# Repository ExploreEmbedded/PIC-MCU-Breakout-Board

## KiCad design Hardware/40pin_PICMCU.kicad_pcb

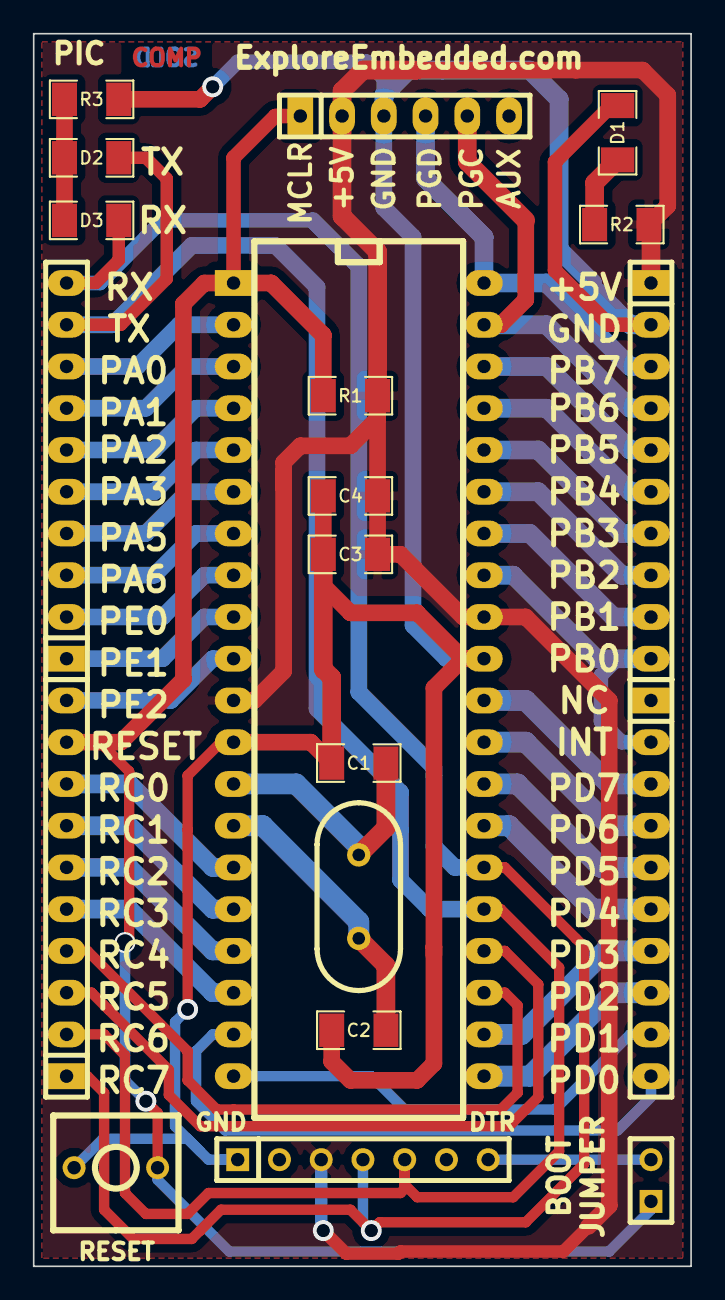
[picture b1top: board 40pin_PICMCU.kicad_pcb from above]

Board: 2 copper layers, 40.0 x 75.0 mm, 20 parts (0 on the bottom side), 41 nets.

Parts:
C1, C2: 22pF; SM1206
C3, C4: 0.1uF; SM1206
D1, D2, D3: LED; SM1206
JP1: JUMPER; SIL-2
P1, P2, P3, P4: CONN_10; SIL-10
P5: CONN_7; SIL-7
P6: ICSP; SIL-6
R1: 10K; SM1206
R2, R3: R; SM1206
SW1: rst; SW_PUSH_SMALL_2pin_xl
U1: 16F877A; DIP-40__600_ELL
X1: 20Mhz; HC-49V

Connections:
/+5V: C3.2, C4.2, P3.1, P5.3, P6.2, R1.2, R2.1, U1.11, U1.32
/D6/PGC: P3.4, P6.5, U1.39
/D7/PGD: P3.3, P6.4, U1.40
/INT: P3.10, P4.2, U1.33
/MCLR: JP1.1, P2.9, P6.1, R1.1, SW1.1, U1.1
/PE2: P2.10, U1.10
/RX: D3.1, P1.10, P2.1, P5.4, U1.26
/TX: D2.1, P1.9, P2.2, P5.5, U1.25
GND: C1.1, C2.1, C3.1, C4.1, D1.2, P3.2, P5.1, P6.3, R3.2, SW1.2, U1.12, U1.31
unnamed: P4.5, U1.28
unnamed: P4.4, U1.29
unnamed: P4.3, U1.30
unnamed: P4.6, U1.27
unnamed: P2.3, U1.24
unnamed: P2.4, U1.23
unnamed: P4.10, U1.19
unnamed: P4.9, U1.20
unnamed: P4.8, U1.21
unnamed: P4.7, U1.22
unnamed: P1.7, U1.3
unnamed: P1.6, U1.4
unnamed: P2.5, U1.18
unnamed: P2.6, U1.17
unnamed: P2.7, U1.16
unnamed: P2.8, U1.15
unnamed: D2.2, D3.2, R3.1
unnamed: JP1.2, P5.7
unnamed: P3.9, U1.34
unnamed: P3.5, U1.38
unnamed: P3.6, U1.37
unnamed: P3.7, U1.36
unnamed: P3.8, U1.35
unnamed: D1.1, R2.2
unnamed: C1.2, U1.13, X1.2
unnamed: C2.2, U1.14, X1.1
unnamed: P1.1, U1.9
unnamed: P1.2, U1.8
unnamed: P1.4, U1.6
unnamed: P1.5, U1.5
unnamed: P1.8, U1.2
unnamed: P1.3, U1.7

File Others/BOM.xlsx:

Id | Designator | Package | Quantity | Designation | Supplier and ref
1 | R1 | SM1206 | 1 | 10K | 50
2 | C1,C2 | SM1206 | 2 | 22pF | 100
3 | C3,C4 | SM1206 | 2 | 0.1uF | 100
4 |  | 40PIN DIP Base | 1 |  | 50
5 | P1,P2,P4,P3 | SIL-10 | 4 | CONN_10 | 1 stck male
6 | X1 | HC-49V | 1 | 20Mhz | 50
7 | U1 | DIP-40__600_ELL | 1 | 16F877A
8 | R2,R3 | SM1206 | 2 | 470E | 100
9 | D1,D2,D3 | SM1206 | 3 | LED | 1 RED and 2 GREEN
12 | SW1 | SW_PUSH_SMALL_2pin_xl | 1 | rst | 50
13 |  | 10pin Box header | 1 |  | 50

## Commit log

2015-06-02 added files
2015-08-11 Gerber file
